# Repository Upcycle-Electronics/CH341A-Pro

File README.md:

# CH341A-Pro

Schematic:
https://github.com/Upcycle-Electronics/CH341A-Pro/blob/master/ch341Apro_schematicV01.pdf

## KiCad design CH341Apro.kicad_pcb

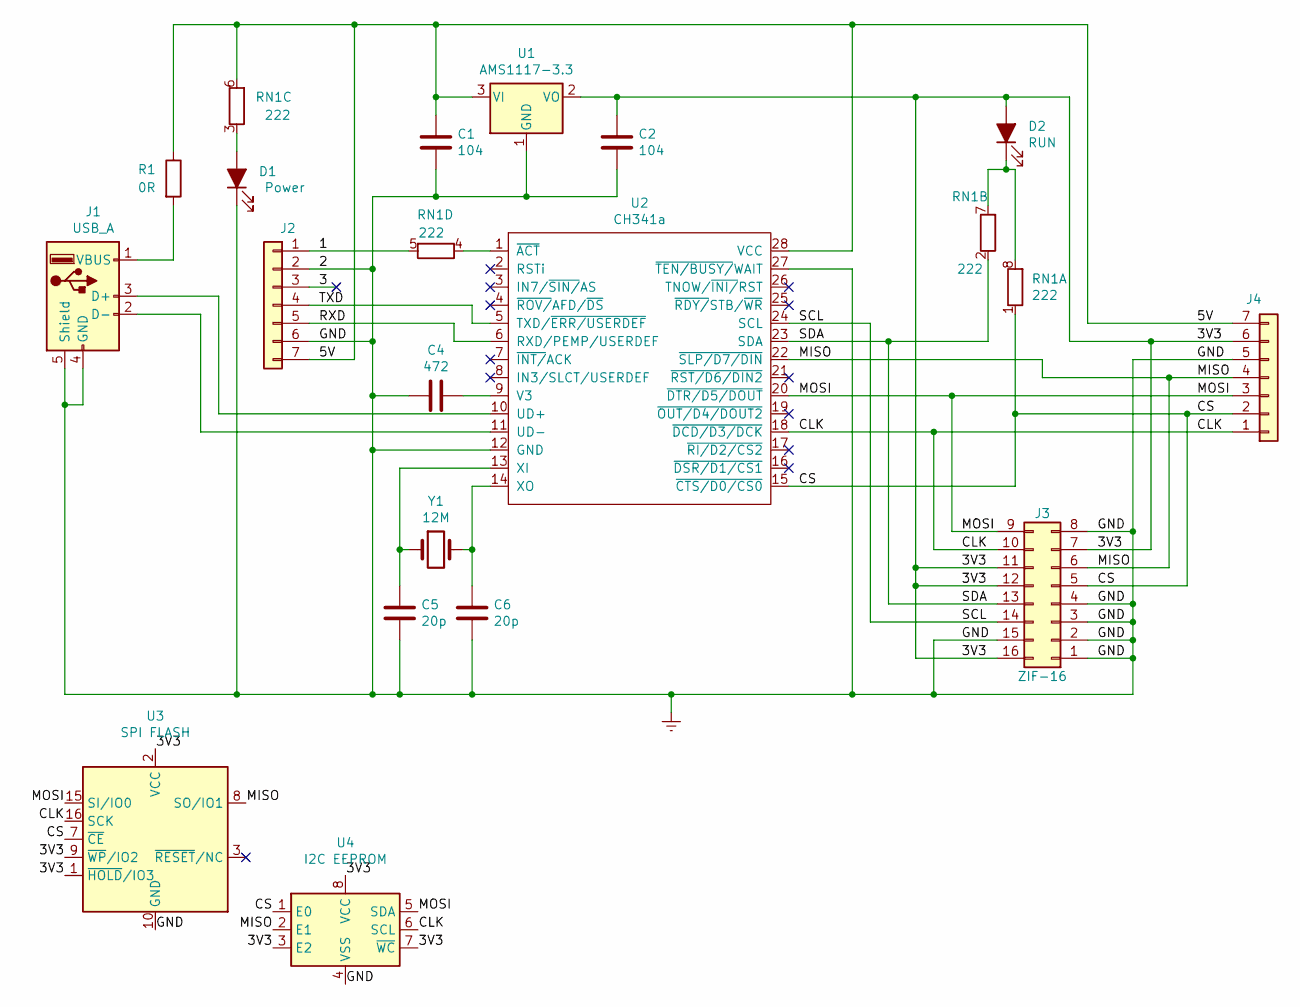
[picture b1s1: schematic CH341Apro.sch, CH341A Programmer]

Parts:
C1, C2: 104; C_0603_1608Metric
C4: 472; C_0603_1608Metric
C5, C6: 20p; C_0603_1608Metric
D1: Power; LED_0603_1608Metric
D2: RUN; LED_0603_1608Metric
J1: USB_A; USB_A_MALE_Generic
J2, J4: Conn_01x07; PinSocket_1x07_P2.54mm_Vertical
J3: ZIF-16; DIP_Socket-16_W4.3_W5.08_W7.62_W10.16_W10.9_3M_216-3340-00-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
R1: 0R; R_0805_2012Metric
RN1: 222; R_Array_Convex_4x0603
U1: AMS1117-3.3; SOT-223-3_TabPin2
U2: CH341a; SOIC-28W_7.5x17.9mm_P1.27mm
U3: SPI FLASH; SOIC-16W_7.5x10.3mm_P1.27mm
U4: I2C EEPROM; SOIC-8_3.9x4.9mm_P1.27mm
Y1: 12M; Crystal_HC49-U_Vertical

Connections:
/1: J2.1, RN1.5 (R4.2)
/3: J2.3
/3V3: C2.1, D2.2 (A), J3.7, J3.11, J3.12, J3.16, J4.6, U1.2 (VO), U3.1 (~HOLD~/IO3), U3.2 (VCC), U3.9 (~WP~/IO2), U4.3 (E2), U4.7 (~WC), U4.8 (VCC)
/5V: C1.1, J2.7, J4.7, R1.1, RN1.6 (R3.2), U1.3 (VI), U2.28 (VCC)
/CLK: J3.10, J4.1, U2.18 (~DCD/D3/DCK), U3.16 (SCK), U4.6 (SCL)
/CS: J3.5, J4.2, RN1.1 (R1.1), U2.15 (~CTS/D0/CS0), U3.7 (~CE), U4.1 (E0)
/MISO: J3.6, J4.4, U2.22 (~SLP/D7/DIN), U3.8 (SO/IO1), U4.2 (E1)
/MOSI: J3.9, J4.3, U2.20 (~DTR/D5/DOUT), U3.15 (SI/IO0), U4.5 (SDA)
/RXD: J2.5, U2.6 (RXD/PEMP/USERDEF)
/SCL: J3.14, U2.24 (SCL)
/SDA: J3.13, RN1.2 (R2.1), U2.23 (SDA)
/TXD: J2.4, U2.5 (TXD/~ERR/USERDEF)
Earth: C1.2, C2.2, C4.2, C5.2, C6.2, D1.1 (K), J1.4 (GND), J1.5 (Shield), J2.2, J2.6, J3.1, J3.2, J3.3, J3.4, J3.8, J3.15, J4.5, U1.1 (GND), U2.12 (GND), U2.27 (~TEN/BUSY/~WAIT), U3.10 (GND), U4.4 (VSS)
unnamed: C4.1, U2.9 (V3)
unnamed: C5.1, U2.13 (XI), Y1.1
unnamed: C6.1, U2.14 (XO), Y1.2
unnamed: D1.2 (A), RN1.3 (R3.1)
unnamed: D2.1 (K), RN1.7 (R2.2), RN1.8 (R1.2)
unnamed: J1.1 (VBUS), R1.2
unnamed: J1.2 (D-), U2.11 (UD-)
unnamed: J1.3 (D+), U2.10 (UD+)
unnamed: RN1.4 (R4.1), U2.1 (~ACT)

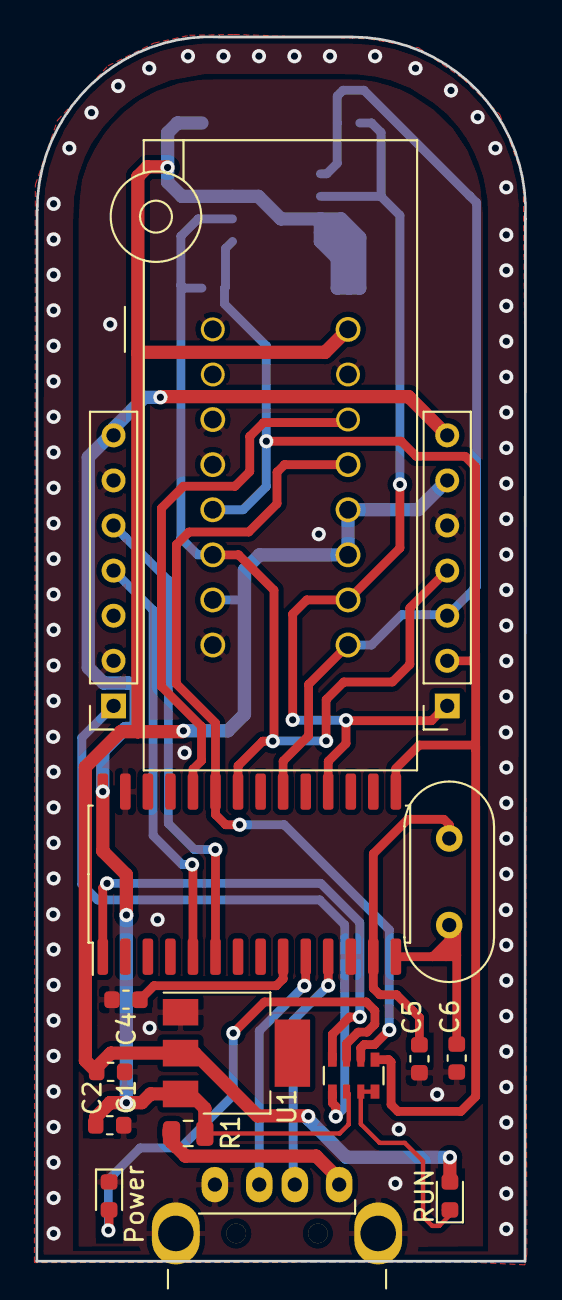
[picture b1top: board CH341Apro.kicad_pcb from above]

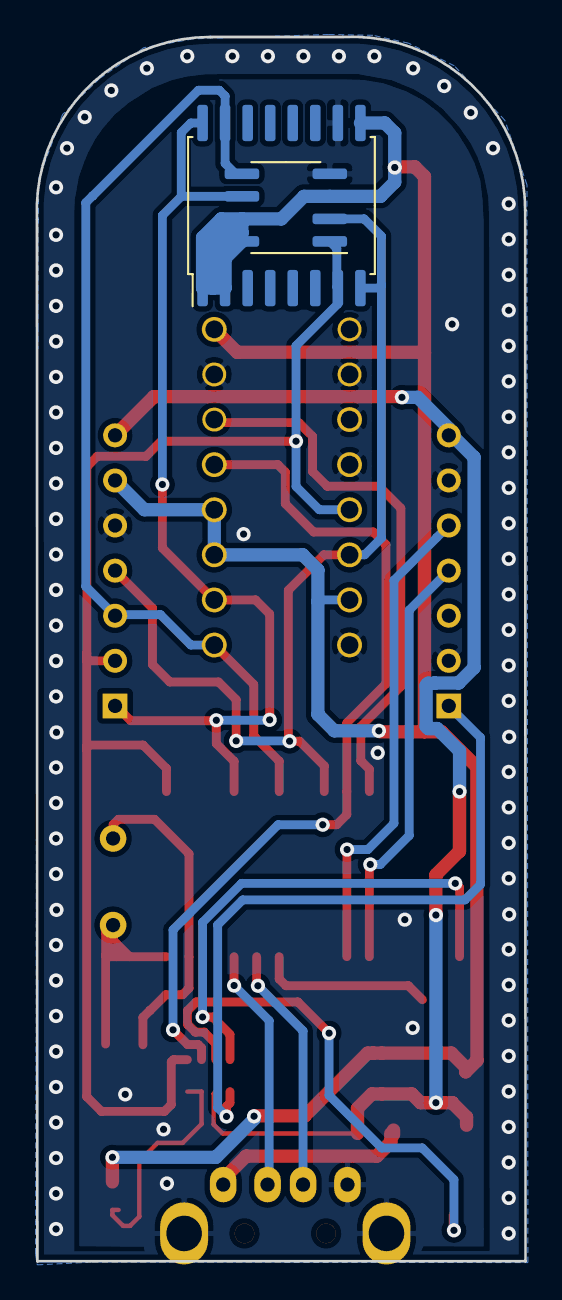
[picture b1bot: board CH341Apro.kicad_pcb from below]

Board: 2 copper layers, 27.5 x 69.0 mm, 18 parts (2 on the bottom side), 21 nets.

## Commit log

2020-07-14 init
